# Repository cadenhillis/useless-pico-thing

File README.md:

# useless-pico-thing
a useless thing for a raspi pico

16x124 OLED and 32 SK6812-EC3210 "Neopixel" LEDs that will fit on-top of a RasPi Pico.

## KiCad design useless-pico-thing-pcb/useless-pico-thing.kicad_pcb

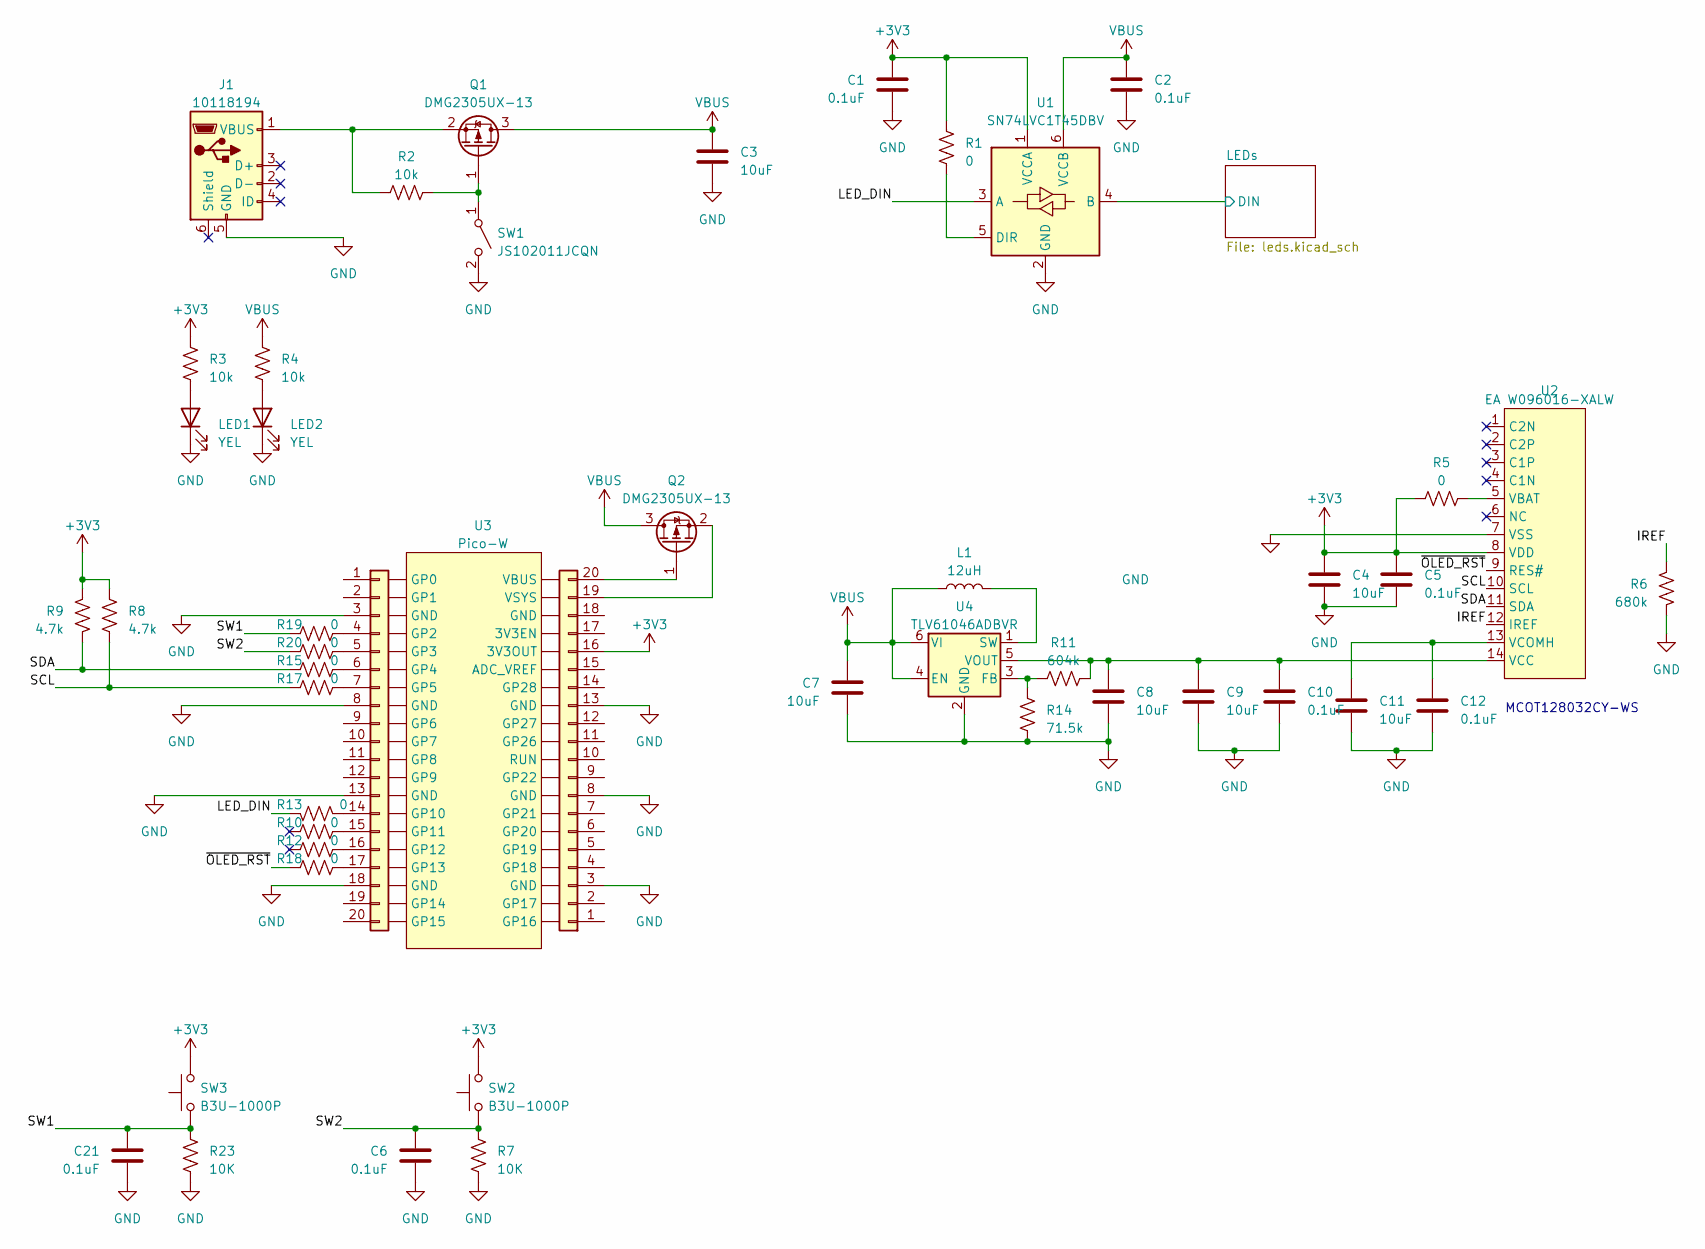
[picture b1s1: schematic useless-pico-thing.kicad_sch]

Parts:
C1, C2, C5, C6, C10, C12, C21: 0.1uF; C_0603_1608Metric
C3, C4, C7, C8, C9, C11: 10uF; C_0603_1608Metric
J1: 10118194; USB_Micro-B_Amphenol_10118194_Horizontal
J2, J3: Conn_01x20; Pico_PinHeader_1x20_P2.54mm_Vertical
L1: 12uH; L_Wuerth_WE-GF-1210
LED1, LED2: YEL; LED_0603_1608Metric
Q1, Q2: DMG2305UX-13; SOT-23
R1, R5, R10, R12, R13, R15, R17, R18, R19, R20: 0; R_0603_1608Metric
R2, R3, R4: 10k; R_0603_1608Metric
R6: 680k; R_0603_1608Metric
R7, R23: 10K; R_0603_1608Metric
R8, R9: 4.7k; R_0603_1608Metric
R11: 604k; R_0603_1608Metric
R14: 71.5k; R_0603_1608Metric
SW1: JS102011JCQN; SW_JS102011JCQN
SW2, SW3: B3U-1000P; SW_SPST_B3U-1000P
U1: SN74LVC1T45DBV; SOT-23-6
U2: EA W096016-XALW; EA_W096016-XALW
U3: Pico-W; RPi_PicoW_SMD
U4: TLV61046ADBVR; SOT-23-6

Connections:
+3V3: C1.1, C4.1, C5.1, J3.16, R1.1, R3.1, R5.1, R8.1, R9.1, SW2.2, SW3.2, U1.1 (VCCA), U2.8 (VDD)
/IREF: R6.1, U2.12 (IREF)
/LED_DIN: R13.2, U1.3 (A)
/LEDs/DIN: U1.4 (B); also elsewhere on the board
/SCL: R8.2, R17.1, U2.10 (SCL)
/SDA: R9.2, R15.1, U2.11 (SDA)
/SW1: C21.1, R19.1, R23.1, SW3.1
/SW2: C6.1, R7.1, R20.1, SW2.1
/~OLED_RST: R18.1, U2.9 (RES#)
GND: C1.2, C2.2, C3.2, C4.2, C5.2, C6.2, C7.2, C8.2, C9.2, C10.2, C11.2, C12.2, C21.2, J1.5 (GND), J2.3, J2.8, J2.13, J2.18, J3.3, J3.8, J3.13, LED1.1 (K), LED2.1 (K), R6.2, R7.2, R14.2, R23.2, SW1.2 (B), U1.2 (GND), U2.7 (VSS), U4.2 (GND); also elsewhere on the board
unnamed: J1.1 (VBUS), Q1.2 (S), R2.1
unnamed: J2.4, R19.2
unnamed: J2.5, R20.2
unnamed: J2.6, R15.2
unnamed: J2.7, R17.2
unnamed: J2.14, R13.1
unnamed: J2.15, R10.2
unnamed: J2.16, R12.2
unnamed: J2.17, R18.2
unnamed: J3.19, Q2.2 (S)
unnamed: J3.20, Q2.1 (G)
unnamed: LED1.2 (A), R3.2
unnamed: LED2.2 (A), R4.2
unnamed: Q1.1 (G), R2.2, SW1.1 (A)
unnamed: R1.2, U1.5 (DIR)
unnamed: R5.2, U2.5 (VBAT)
unnamed: C8.1, C9.1, C10.1, R11.2, U2.14 (VCC), U4.5 (VOUT)
unnamed: C11.1, C12.1, U2.13 (VCOMH)
unnamed: R11.1, R14.1, U4.3 (FB)
unnamed: L1.2, U4.1 (SW)
VBUS: C2.1, C3.1, C7.1, L1.1, Q1.3 (D), Q2.3 (D), R4.1, U1.6 (VCCB), U4.4 (EN), U4.6 (VI); also elsewhere on the board

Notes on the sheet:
MCOT128032CY-WS

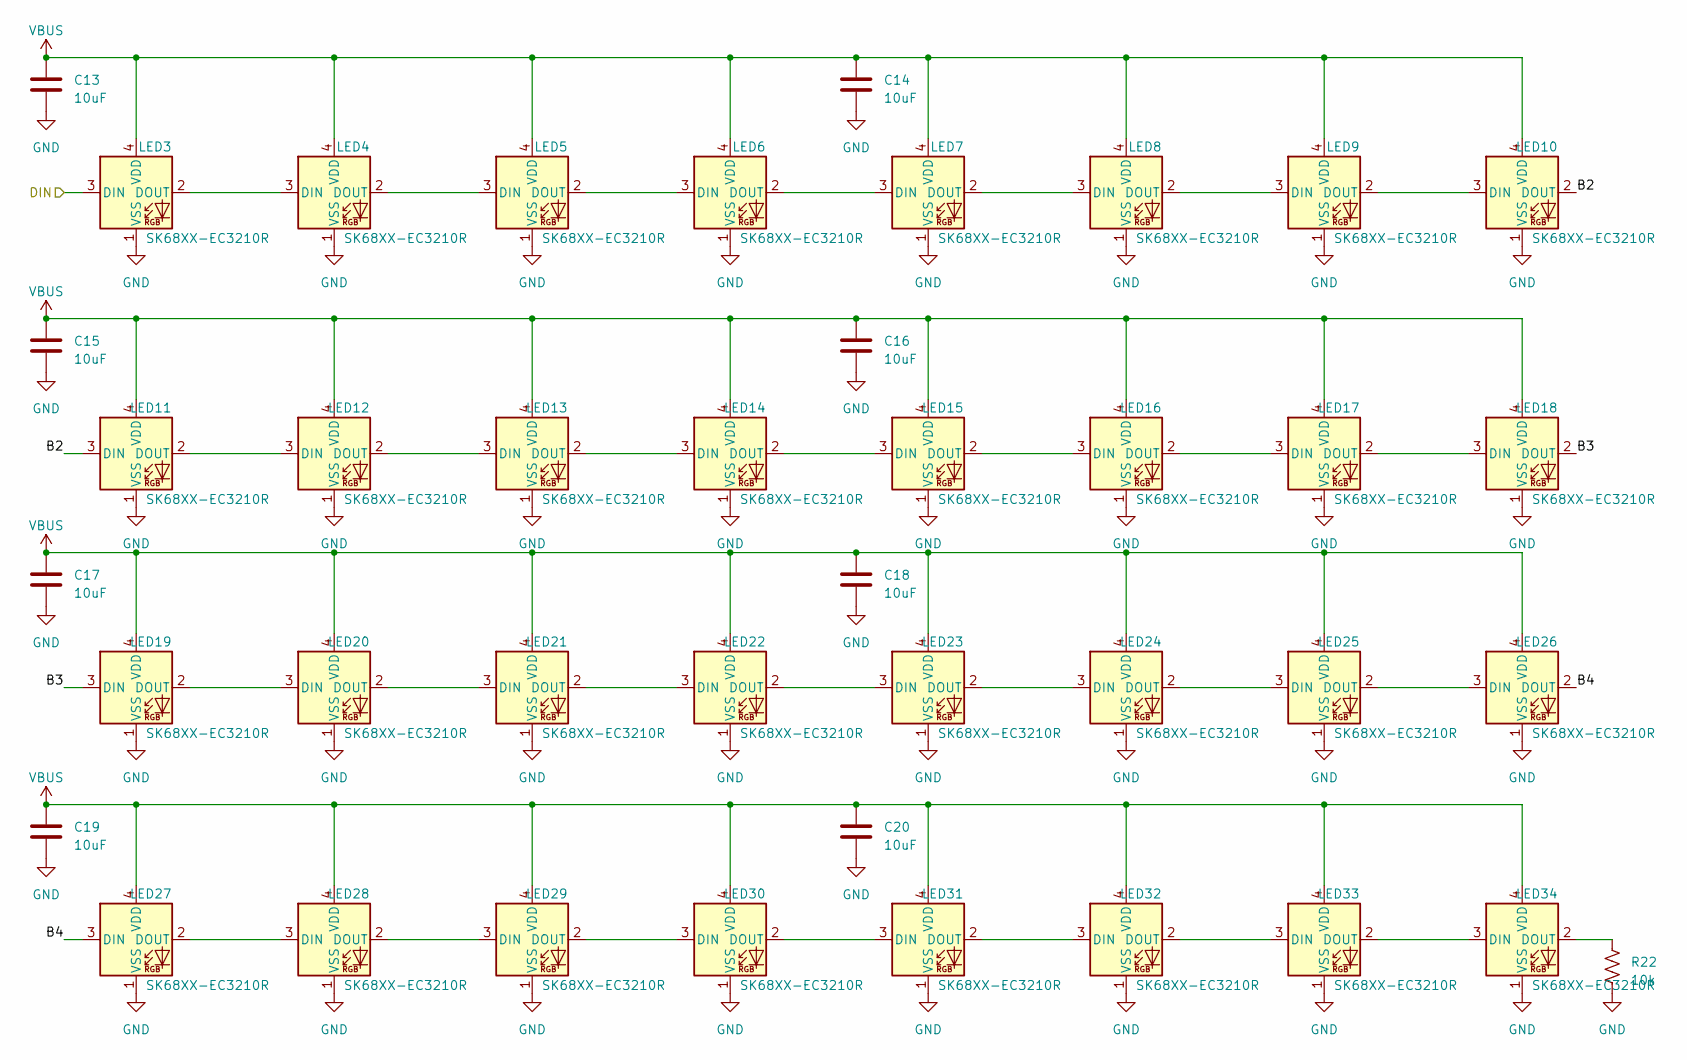
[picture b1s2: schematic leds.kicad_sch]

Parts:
C13, C14, C15, C16, C17, C18, C19, C20: 10uF; C_0603_1608Metric
LED3, LED4, LED5, LED6, LED7, LED8, LED9, LED10, LED11, LED12, LED13, LED14, LED15, LED16, LED17, LED18, LED19, LED20, LED21, LED22, LED23, LED24, LED25, LED26, LED27, LED28, LED29, LED30, LED31, LED32, LED33, LED34: SK68XX-EC3210R; LED_SK68xx-EC3210x
R22: 10k; R_0603_1608Metric

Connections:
/LEDs/B2: LED10.2 (DOUT), LED11.3 (DIN)
/LEDs/B3: LED18.2 (DOUT), LED19.3 (DIN)
/LEDs/B4: LED26.2 (DOUT), LED27.3 (DIN)
/LEDs/DIN: LED3.3 (DIN); also elsewhere on the board
GND: C13.2, C14.2, C15.2, C16.2, C17.2, C18.2, C19.2, C20.2, LED3.1 (VSS), LED4.1 (VSS), LED5.1 (VSS), LED6.1 (VSS), LED7.1 (VSS), LED8.1 (VSS), LED9.1 (VSS), LED10.1 (VSS), LED11.1 (VSS), LED12.1 (VSS), LED13.1 (VSS), LED14.1 (VSS), LED15.1 (VSS), LED16.1 (VSS), LED17.1 (VSS), LED18.1 (VSS), LED19.1 (VSS), LED20.1 (VSS), LED21.1 (VSS), LED22.1 (VSS), LED23.1 (VSS), LED24.1 (VSS), LED25.1 (VSS), LED26.1 (VSS), LED27.1 (VSS), LED28.1 (VSS), LED29.1 (VSS), LED30.1 (VSS), LED31.1 (VSS), LED32.1 (VSS), LED33.1 (VSS), LED34.1 (VSS), R22.2; also elsewhere on the board
unnamed: LED3.2 (DOUT), LED4.3 (DIN)
unnamed: LED4.2 (DOUT), LED5.3 (DIN)
unnamed: LED5.2 (DOUT), LED6.3 (DIN)
unnamed: LED6.2 (DOUT), LED7.3 (DIN)
unnamed: LED7.2 (DOUT), LED8.3 (DIN)
unnamed: LED8.2 (DOUT), LED9.3 (DIN)
unnamed: LED9.2 (DOUT), LED10.3 (DIN)
unnamed: LED11.2 (DOUT), LED12.3 (DIN)
unnamed: LED12.2 (DOUT), LED13.3 (DIN)
unnamed: LED13.2 (DOUT), LED14.3 (DIN)
unnamed: LED14.2 (DOUT), LED15.3 (DIN)
unnamed: LED15.2 (DOUT), LED16.3 (DIN)
unnamed: LED16.2 (DOUT), LED17.3 (DIN)
unnamed: LED17.2 (DOUT), LED18.3 (DIN)
unnamed: LED19.2 (DOUT), LED20.3 (DIN)
unnamed: LED20.2 (DOUT), LED21.3 (DIN)
unnamed: LED21.2 (DOUT), LED22.3 (DIN)
unnamed: LED22.2 (DOUT), LED23.3 (DIN)
unnamed: LED23.2 (DOUT), LED24.3 (DIN)
unnamed: LED24.2 (DOUT), LED25.3 (DIN)
unnamed: LED25.2 (DOUT), LED26.3 (DIN)
unnamed: LED27.2 (DOUT), LED28.3 (DIN)
unnamed: LED28.2 (DOUT), LED29.3 (DIN)
unnamed: LED29.2 (DOUT), LED30.3 (DIN)
unnamed: LED30.2 (DOUT), LED31.3 (DIN)
unnamed: LED31.2 (DOUT), LED32.3 (DIN)
unnamed: LED32.2 (DOUT), LED33.3 (DIN)
unnamed: LED33.2 (DOUT), LED34.3 (DIN)
unnamed: LED34.2 (DOUT), R22.1
VBUS: C13.1, C14.1, C15.1, C16.1, C17.1, C18.1, C19.1, C20.1, LED3.4 (VDD), LED4.4 (VDD), LED5.4 (VDD), LED6.4 (VDD), LED7.4 (VDD), LED8.4 (VDD), LED9.4 (VDD), LED10.4 (VDD), LED11.4 (VDD), LED12.4 (VDD), LED13.4 (VDD), LED14.4 (VDD), LED15.4 (VDD), LED16.4 (VDD), LED17.4 (VDD), LED18.4 (VDD), LED19.4 (VDD), LED20.4 (VDD), LED21.4 (VDD), LED22.4 (VDD), LED23.4 (VDD), LED24.4 (VDD), LED25.4 (VDD), LED26.4 (VDD), LED27.4 (VDD), LED28.4 (VDD), LED29.4 (VDD), LED30.4 (VDD), LED31.4 (VDD), LED32.4 (VDD), LED33.4 (VDD), LED34.4 (VDD); also elsewhere on the board

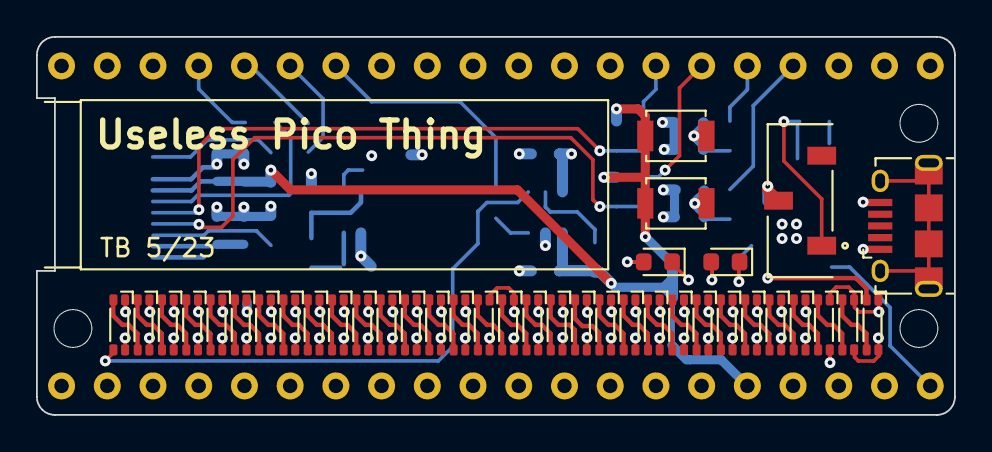
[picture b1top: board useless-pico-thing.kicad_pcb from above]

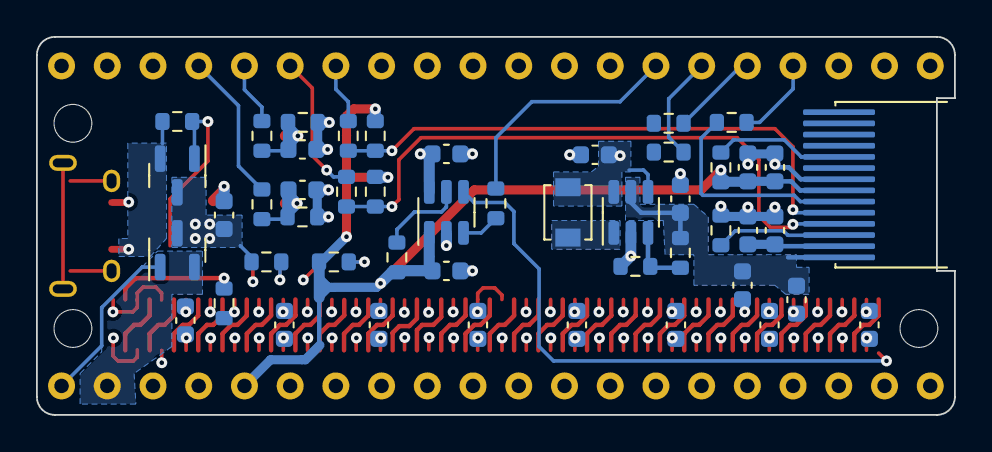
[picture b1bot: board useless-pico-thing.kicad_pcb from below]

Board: 4 copper layers, 51.0 x 21.0 mm, 88 parts (49 on the bottom side), 63 nets.

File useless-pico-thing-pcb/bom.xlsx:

Ref | Qnty | Value | Footprint | P/N
C1, C2, C5, C6, C10, C12, C21 | 7 | 0.1uF | 0603 | 0603YC104KAT2A
C3, C4, C7, C8, C9, C11, C13, C14, C15, C16, C17, C18, C19, C20 | 14 | 10uF | 0603 | 0603YW106MAT2A
J1 | 1 | 10118194 | Micro-B_Amphenol_10118194_Horizontal | 10118194-0001LF
L1 | 1 | 12uH | 1210 | 744032120
LED1, LED2 | 2 | YEL | 0603 | LTST-C191KSKT
LED3, LED4, LED5, LED6, LED7, LED8, LED9, LED10, LED11, LED12, LED13, LED14, LE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 | 32 | SK68XX-EC3210R | 3210 | 1528-4892-ND
Q1, Q2 | 2 | DMG2305UX-13 | SOT-23 | DMG2305UX-13
R2, R3, R4, R7, R22, R23 | 6 | 10k | 0603 | RNCP0603FTD10K0
R1, R5, R10, R12, R13, R15, R17, R18, R19, R20 | 10 | 0 | 0603 | RMCF0603ZT0R00
R6 | 1 | 680k | 0603 | RMCF0603FT680K
R8, R9 | 2 | 4.7k | 0603 | RMCF0603FT4K70
R11 | 1 | 604k | 0603 | RMCF0603FT604K
R14 | 1 | 71.5k | 0603 | RMCF0603FT71K5
SW1 | 1 | JS102011JCQN | JS102011JCQN | JS102011JCQN
SW2, SW3 | 2 | B3U-1000P | B3U-1000P | B3U-1000P
U1 | 1 | SN74LVC1T45DBV | SOT-23-6 | SN74LVC1T45DBV
U2 | 1 | EA W096016-XALW | EA_W096016-XALW | EA W096016-XALW
U4 | 1 | TLV61046ADBVR | Package_TO_SOT_SMD:SOT-23-6 | TLV61046ADBVR

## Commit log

2023-05-07 kicad design files
